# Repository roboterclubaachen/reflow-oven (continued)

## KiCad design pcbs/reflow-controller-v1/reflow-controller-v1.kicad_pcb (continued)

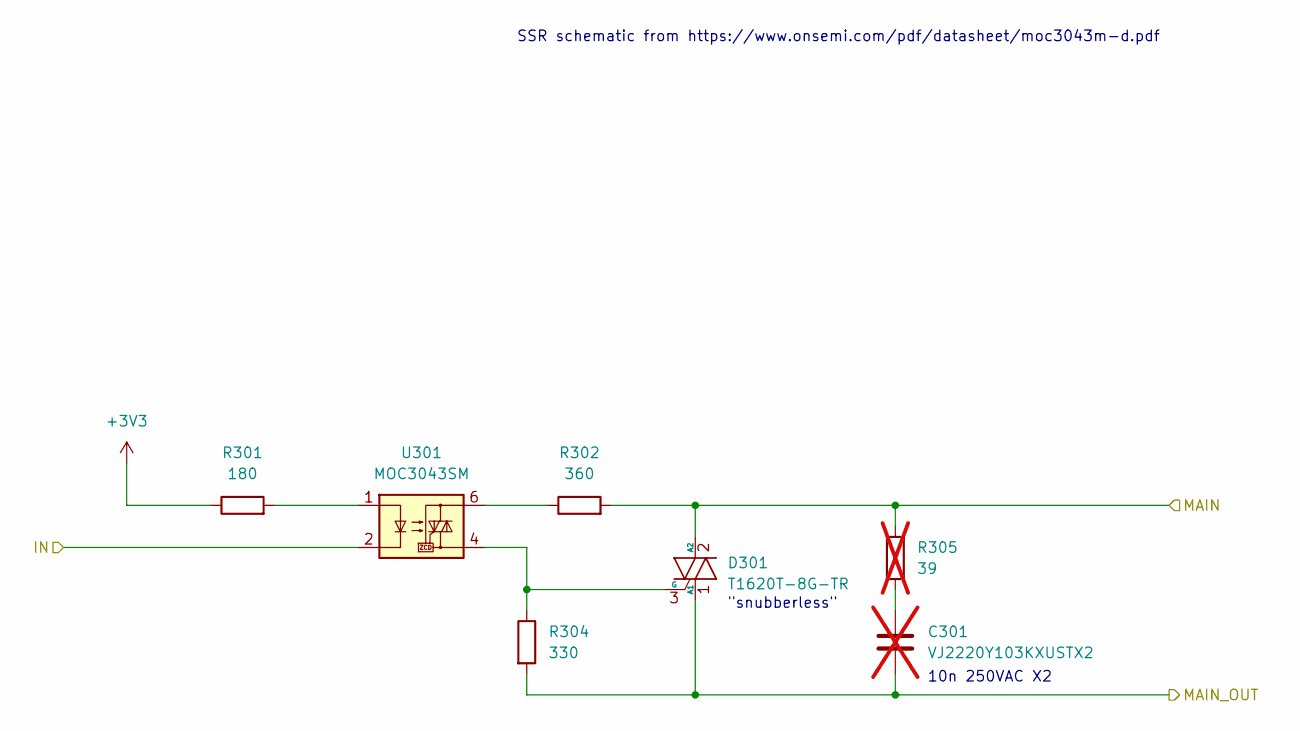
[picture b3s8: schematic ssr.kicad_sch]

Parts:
C301: VJ2220Y103KXUSTX2; C_2220_5750Metric; not fitted
D301: T1620T-8G-TR; TO-263-2
R301: 180; R_0603_1608Metric
R302: 360; R_1206_3216Metric
R304: 330; R_1206_3216Metric
R305: 39; R_1206_3216Metric; not fitted
U301: MOC3043SM; DIP-6_W7.62mm_SMDSocket_SmallPads

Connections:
+3V3: R301.1; also elsewhere on the board
/Phase_L: D301.2 (A2), R302.2, R305.1; also elsewhere on the board
/SSR 1/IN: U301.2; also elsewhere on the board
/SSR 1/MAIN_OUT: C301.2, D301.1 (A1), R304.2; also elsewhere on the board
unnamed: C301.1, R305.2
unnamed: D301.3 (G), R304.1, U301.4
unnamed: R301.2, U301.1
unnamed: R302.1, U301.6

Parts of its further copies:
C401, C501, C601: VJ2220Y103KXUSTX2; C_2220_5750Metric; not fitted
D401, D501, D601: T1620T-8G-TR; TO-263-2
R401, R501, R601: 180; R_0603_1608Metric
R402, R502, R602: 330; R_1206_3216Metric
R403, R503, R603: 360; R_1206_3216Metric
R404, R504, R604: 39; R_1206_3216Metric; not fitted
U401, U501, U601: MOC3043SM; DIP-6_W7.62mm_SMDSocket_SmallPads

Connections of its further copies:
+3V3: R401.1, R501.1, R601.1; also elsewhere on the board
/Phase_L: D401.2 (A2), D501.2 (A2), D601.2 (A2), R403.2, R404.1, R503.2, R504.1, R603.2, R604.1; also elsewhere on the board
/SSR 2/IN: U401.2; also elsewhere on the board
/SSR 2/MAIN_OUT: C401.2, D401.1 (A1), R402.2; also elsewhere on the board
/SSR 3/IN: U501.2; also elsewhere on the board
/SSR 3/MAIN_OUT: C501.2, D501.1 (A1), R502.2; also elsewhere on the board
/SSR 4/IN: U601.2; also elsewhere on the board
/SSR 4/MAIN_OUT: C601.2, D601.1 (A1), R602.2; also elsewhere on the board
unnamed: C401.1, R404.2
unnamed: C501.1, R504.2
unnamed: C601.1, R604.2
unnamed: D401.3 (G), R402.1, U401.4
unnamed: D501.3 (G), R502.1, U501.4
unnamed: D601.3 (G), R602.1, U601.4
unnamed: R401.2, U401.1
unnamed: R403.1, U401.6
unnamed: R501.2, U501.1
unnamed: R503.1, U501.6
unnamed: R601.2, U601.1
unnamed: R603.1, U601.6

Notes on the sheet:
"snubberless"
SSR schematic from https://www.onsemi.com/pdf/datasheet/moc3043m-d.pdf
10n 250VAC X2

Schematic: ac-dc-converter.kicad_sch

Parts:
C201, C205, C206, C207, C212: 100n; C_0603_1608Metric
C202: EEEFK1E470P; CP_Elec_6.3x5.9
C203, C204, C213: 10u 35V; C_1206_3216Metric
C208, C209, C210, C211, C214: 22u 10V; C_1206_3216Metric
D201: LED green; LED_0603_1608Metric
D202: SMAJ5.0CA; D_SMA
FB201: WE-RFI 744762439A; L_1008_2520Metric
J201: PinHeader 1x02 P2.54mm; Molex_KK-254_AE-6410-02A_1x02_P2.54mm_Vertical
L201: NRS5030T6R8MMGJ; L_Taiyo-Yuden_NR-50xx
PS202: IRM-10-5; Converter_ACDC_MeanWell_IRM-10-xx_THT
Q201: PMV65XP; SOT-23
R201: 511k; R_0603_1608Metric
R202: 88.7k; R_0603_1608Metric
R203: 0; R_0603_1608Metric
R204: 10k; R_0603_1608Metric
R205: 2.7k; R_0603_1608Metric
R206: 31.2k; R_0603_1608Metric
U201: TPS62933DRLR; SOT-583-8
U202: AZ1117-3.3; SOT-223-3_TabPin2

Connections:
+3.3VA: FB201.1; also elsewhere on the board
+3V3: C208.1, C209.1, C210.1, C211.1, C212.1, L201.2, R205.1, R206.1; also elsewhere on the board
+5V: C201.1, C202.1, C203.1, C204.1, C205.1, C213.1, PS202.4 (+Vo), Q201.2 (S), R201.1, U201.3 (VIN), U202.3 (VI); also elsewhere on the board
/AC DC Converter/BST: C207.1, U201.6 (BST)
/AC DC Converter/EN: R201.2, R202.1, U201.2 (EN)
/AC DC Converter/LED: D201.2 (A), R205.2
/AC DC Converter/RT: R203.1, U201.1 (RT)
/AC DC Converter/SS: C206.1, U201.7 (SS)
/AC DC Converter/SW: C207.2, L201.1, U201.5 (SW)
/Phase_L: PS202.2 (AC/L); also elsewhere on the board
/Phase_N: PS202.1 (AC/N); also elsewhere on the board
GND: C201.2, C202.2, C203.2, C204.2, C205.2, C206.2, C208.2, C209.2, C210.2, C211.2, C212.2, C213.2, C214.2, D201.1 (K), D202.1 (A1), J201.2, PS202.3 (-Vo), Q201.1 (G), R202.2, R203.2, R204.2, U201.4 (GND), U202.1 (GND); also elsewhere on the board
unnamed: D202.2 (A2), J201.1, Q201.3 (D)
unnamed: R204.1, R206.2, U201.8 (FB)
unnamed: C214.1, FB201.2, U202.2 (VO)

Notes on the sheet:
~8kΩ@16MHz
Debug Power In
GND for 1200kHz Flaoting for 500kHz
47µF

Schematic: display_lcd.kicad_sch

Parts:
U4: ILI9341 Module

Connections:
+3V3: U4.1 (VCC); also elsewhere on the board
/Display LCD/DC/RS: U4.5 (DC/RS); also elsewhere on the board
/Display LCD/LED: U4.8 (LED); also elsewhere on the board
/Display LCD/MISO: U4.9 (MISO); also elsewhere on the board
/Display LCD/MOSI: U4.6 (MOSI); also elsewhere on the board
/Display LCD/SCK: U4.7 (SCK); also elsewhere on the board
/Display LCD/SD_MISO: U4.17 (SD_MISO); also elsewhere on the board
/Display LCD/SD_MOSI: U4.16 (SD_MOSI); also elsewhere on the board
/Display LCD/SD_SCK: U4.18 (SD_SCK); also elsewhere on the board
/Display LCD/T_CLK: U4.10 (T_CLK); also elsewhere on the board
/Display LCD/T_CS: U4.11 (T_CS); also elsewhere on the board
/Display LCD/T_DIN: U4.12 (T_DIN); also elsewhere on the board
/Display LCD/T_DO: U4.13 (T_DO); also elsewhere on the board
/Display LCD/T_IRQ: U4.14 (T_IRQ); also elsewhere on the board
/Display LCD/Touch: U4.15 (Touch); also elsewhere on the board
/Display LCD/~CS: U4.3 (~CS); also elsewhere on the board
/Display LCD/~RESET: U4.4 (~RESET); also elsewhere on the board
GND: U4.2 (GND); also elsewhere on the board

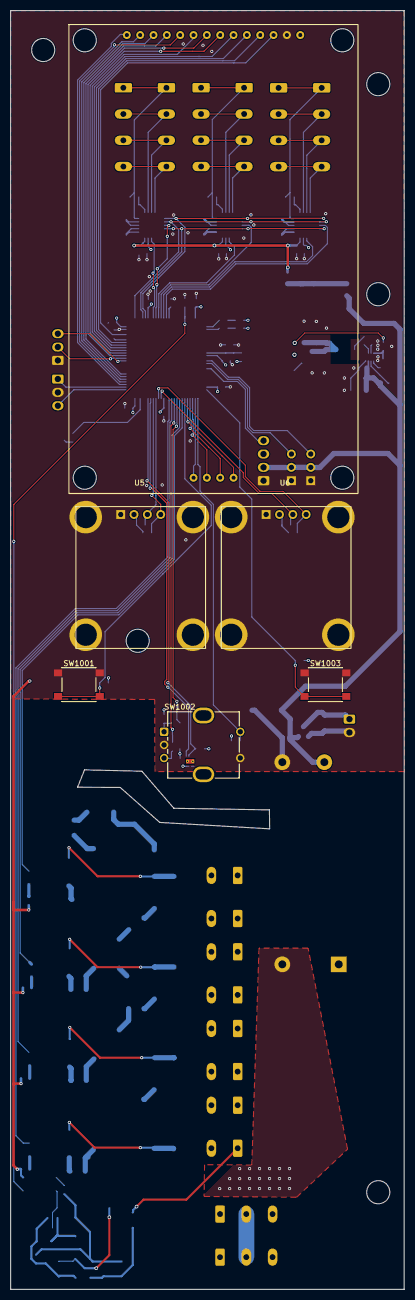
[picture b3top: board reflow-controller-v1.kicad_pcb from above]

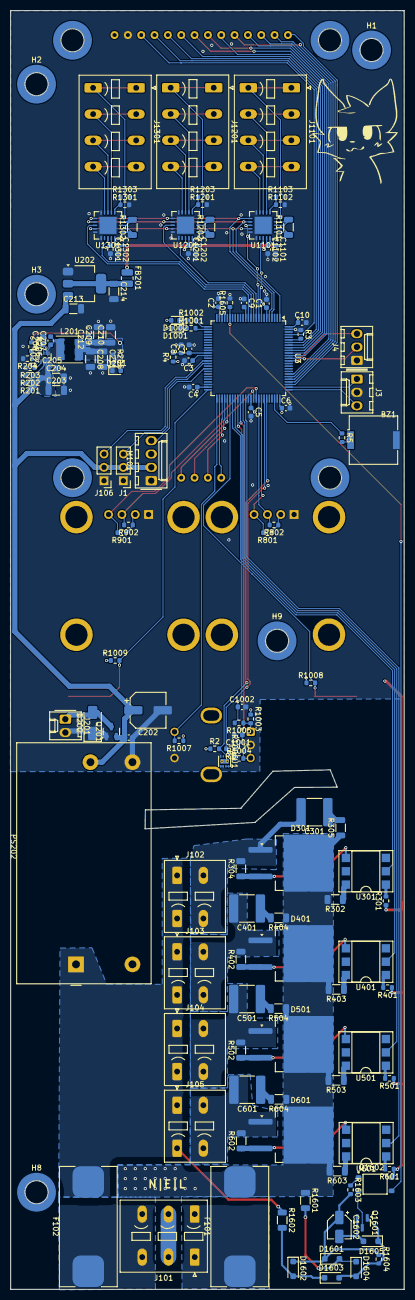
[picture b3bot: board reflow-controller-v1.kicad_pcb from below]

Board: 4 copper layers, 74.9 x 243.5 mm, 149 parts (143 on the bottom side), 124 nets.

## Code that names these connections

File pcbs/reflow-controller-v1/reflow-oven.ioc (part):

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Mcu.Name=STM32G474V(B-C-E)Tx
Mcu.Package=LQFP100
Mcu.UserName=STM32G474VETx
PA0.Signal=S_TIM2_ETR
PA12.Signal=S_TIM16_CH1
PA13.Mode=Serial_Wire
PA13.Signal=SYS_JTMS-SWDIO
PA14.Mode=Serial_Wire
PA14.Signal=SYS_JTCK-SWCLK
PA15.Signal=GPIO_Input
PA4.Signal=GPIO_Output
PA5.Signal=GPIO_Output
PA8.Mode=I2C
PA8.Signal=I2C2_SDA
PA9.Mode=I2C
PA9.Signal=I2C2_SCL
PB11.Signal=GPIO_Input
PB12.Signal=GPIO_Input
PB13.Mode=Full_Duplex_Master
PB13.Signal=SPI2_SCK
PB14.Mode=Full_Duplex_Master
PB14.Signal=SPI2_MISO
PB15.Mode=Full_Duplex_Master
PB15.Signal=SPI2_MOSI
PB3.Mode=Full_Duplex_Master
PB3.Signal=SPI1_SCK
PB4.Mode=Full_Duplex_Master
PB4.Signal=SPI1_MISO
PB5.Mode=Full_Duplex_Master
PB5.Signal=SPI1_MOSI
PB6.Signal=GPIO_Output
PB7.Signal=GPIO_Output
PB8-BOOT0.Signal=GPIO_Input
PC10.Mode=Full_Duplex_Master
PC10.Signal=SPI3_SCK
PC11.Mode=Full_Duplex_Master
PC11.Signal=SPI3_MISO
PC12.Mode=Full_Duplex_Master
PC12.Signal=SPI3_MOSI
PC14-OSC32_IN.Signal=GPIO_Input
PC15-OSC32_OUT.Signal=GPIO_Output
PC6.Mode=I2C
PC6.Signal=I2C4_SCL
PC7.Mode=I2C
PC7.Signal=I2C4_SDA
PC8.Mode=I2C
PC8.Signal=I2C3_SCL
PC9.Mode=I2C
PC9.Signal=I2C3_SDA
PD0.Signal=GPIO_Output
PD10.Signal=GPIO_Input
PD11.Signal=GPIO_Input
PD12.Signal=S_TIM4_CH1
PD13.Signal=S_TIM4_CH2
PD14.Signal=GPIO_Output
PD15.Signal=GPIO_Output
PD5.Mode=Asynchronous
PD5.Signal=USART2_TX
PD6.Mode=Asynchronous
PD6.Signal=USART2_RX
PD7.Signal=GPIO_Output
PD8.Signal=GPIO_Input
PD9.Signal=GPIO_Input
PE0.Signal=GPIO_Input
PE11.Signal=S_TIM1_CH2
PE2.Mode=Full_Duplex_Master
PE2.Signal=SPI4_SCK
PE5.Mode=Full_Duplex_Master
PE5.Signal=SPI4_MISO
PE6.Mode=Full_Duplex_Master
PE6.Signal=SPI4_MOSI
PE8.Signal=S_TIM5_CH3
PE9.Signal=S_TIM5_CH4
PF0-OSC_IN.Signal=GPIO_Input
PF1-OSC_OUT.Signal=GPIO_Output
PF10.Signal=GPIO_Output
PF9.Signal=GPIO_Input
PG10-NRST.Signal=GPIO_Input
RCC.HSE_VALUE=8000000
RCC.SYSCLKFreq_VALUE=16000000
board=custom

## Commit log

2023-08-22 [pcbs] reflow-controller-v1: Schematic created
2024-03-19 added temp sensor
2024-07-02 kicad version bump
2024-07-02 footprint assignement fixed; buzzer added
2024-07-04 [pcbs] Add initial placement
2024-07-09 SSR schematic: add link to datasheet/reference schematic
2024-07-10 [pcb] move most smd parts to bottom layer
2024-07-17 Adjust design rules: remove small trace and via sizes
2024-07-19 add debug power input
2024-07-30 WIP pcb design & routing
2024-07-31 update routing with new mechanical positioning
2024-07-31 increase isolation distance
2024-08-03 add debug uart & swd
2024-08-03 update debug power footprint
2024-08-04 include cubemx project
2024-08-04 label uart & swd
2024-08-04 move Fan PWM to different timer
2024-08-04 add labels to specify encoder periferal
2024-08-04 add labels to specify buzzer periferal
2024-08-04 correct false pin directions
2024-08-12 implement first layout feedback
2024-08-13 improve dfn qfn fanouts
2024-08-13 move beeper
2024-08-14 add zero crossing detector
2024-08-15 fix zero crossing detector 3.3 voltage supply
2024-08-15 add ldo for analog voltage
2024-08-15 move misplaced 5V output caps
2024-08-15 update analog voltage ldo placement&routing
2024-08-15 improve powerdelivery to optotriacs
2024-08-15 add clear border between HV&LV
2024-08-24 design test ui plane for fitting&positioning of the displays
2024-08-24 update pcb size&display positioning
2024-09-04 update hv placment&routing + add initiall hv lv seperation
2024-09-05 Add README and license files
2024-09-06 update display placing & prelim. routing
2024-09-06 pcb routing touchups
2024-09-22 small routing improvements
2024-10-04 Squashed 'code/reflow-display/' content from commit 2c43d99
    git-subtree-dir: code/reflow-display
    git-subtree-split: 2c43d994d7cec9e0e16765643a6efd9b48b495c8
2024-10-04 Edited gitignore, Initial commit
2024-10-06 Made plot.hpp more customizable, fixed a lot of bugs
2024-10-08 Organized source files, project now compiles
2024-10-11 Screens are now children of views - using views with view stack
2024-10-16 Initial, prepared for rendering lvgl on ili9341
2024-10-22 Proto procScreen, does not draw on display. Changed timer to seconds
2024-10-29 Refactor code structure and initialize display buffer properly
    - Refactored the code structure to organize source files and make the project compile successfully.
    - Updated the initialization of the display buffer in the lvgl driver to use the correct buffer size.
    - Overhauled ProcScreen
    Closes #123
2024-11-12 Major refraction of code to get lvgl to work, memory related issue when running the code
2024-11-18 Migrate code to "code" dir, upgraded to lvgl 9.2, set up example for ili9341
2024-11-19 Display now finally working with lvgl! We have liftoff!
2024-11-24 Added finished process screen from simulation
2024-11-27 Moved test screen to screens
2024-12-10 Enhance touch screen functionality and update process screen layout
    - Added raw touch value display to the test screen.
    - Improved touch calibration settings for better accuracy.
    - Updated process screen to include current temperature display and adjusted layout.
    - Refactored screen creation to streamline UI components.
2024-12-19 Added profile select screen. Added timer and profile functionality
2025-01-09 Update README.md
    Added short description to the added code
2025-05-09 split pcbs into two for safety
2025-05-11 Initial hv placing
2025-05-12 improve component selection
2025-05-13 route hv pcb
